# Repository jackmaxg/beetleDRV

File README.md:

# beetleDRV
Tiny brushed motor controller for 3lbs beetle weight combat robots

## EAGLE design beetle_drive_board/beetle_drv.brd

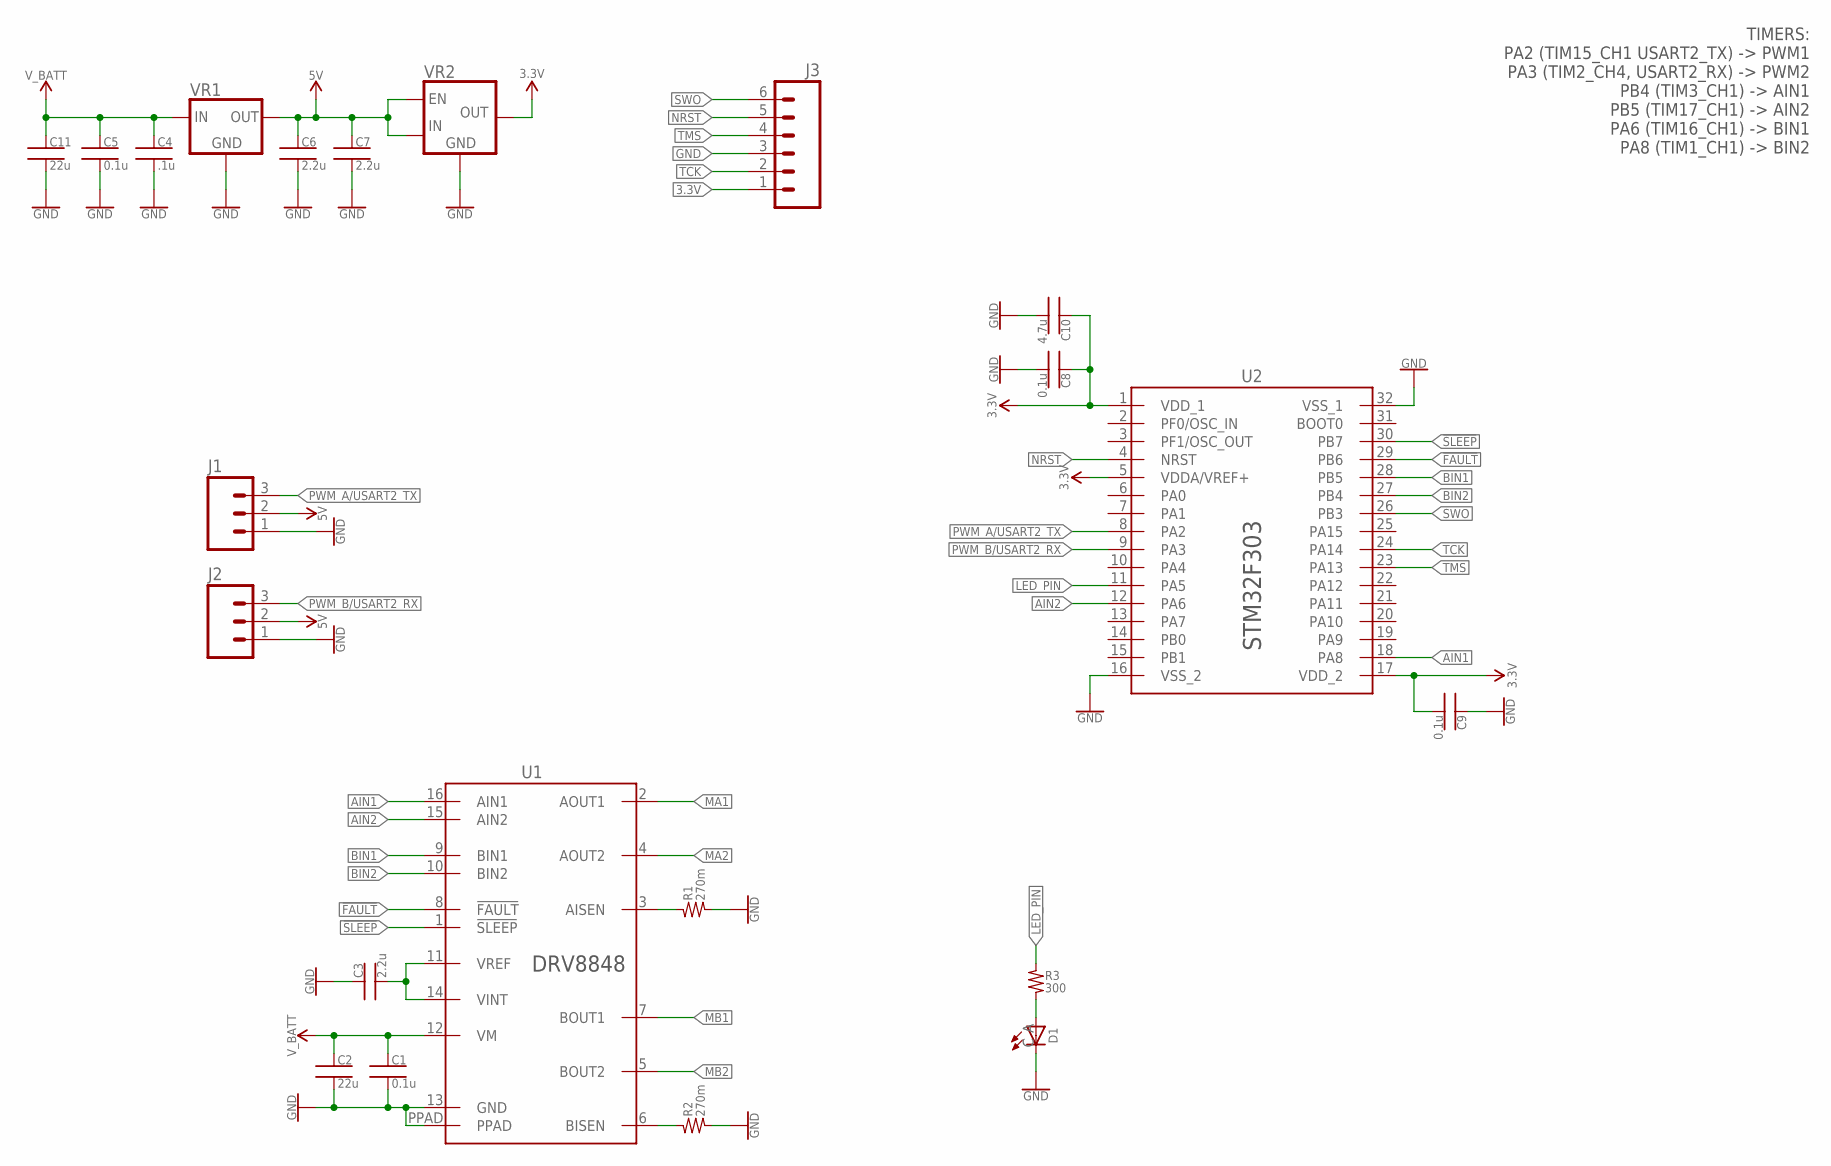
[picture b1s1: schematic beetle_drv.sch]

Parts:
C1, C5, C8, C9: 0.1u; 0603
C2, C11: 22u; 1210
C3, C6, C7: 2.2u; 0603
C4: .1u; 0603
C10: 4.7u; 0603
D1: LED1206; LED-1206
J1, J2: M03; 1X03
J3: SM06B-SRSS-TB
R1, R2: 270m; 1210
R3: 300; 0603
U1: DRV8848; PWP0016C
U2: STM32F303_LQFP32; LQFP32
VR1: 78XX_VREG_SOT223; SOT223-4
VR2: TLV733P_SOT23; SOT23-5

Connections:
3.3V: C8.1, C9.2, C10.1, J3.1, U2.1 (VDD_1), U2.5 (VDDA/VREF+), U2.17 (VDD_2), VR2.5 (OUT)
5V: C6.1, C7.1, J1.2, J2.2, VR1.3 (OUT), VR2.1 (IN), VR2.3 (EN)
!FAULT: U1.8 (!FAULT), U2.29 (PB6)
!SLEEP: U1.1 (!SLEEP), U2.30 (PB7)
AIN1: U1.16 (AIN1), U2.18 (PA8)
AIN2: U1.15 (AIN2), U2.12 (PA6)
AI_SEN: R1.1, U1.3 (AISEN)
BIN1: U1.9 (BIN1), U2.28 (PB5)
BIN2: U1.10 (BIN2), U2.27 (PB4)
BISEN: R2.1, U1.6 (BISEN)
GND: C1.2, C2.2, C3.1, C4.2, C5.2, C6.2, C7.2, C8.2, C9.1, C10.2, C11.2, D1.C, J1.1, J2.1, J3.3, R1.2, R2.2, U1.13 (GND), U1.PPAD, U2.16 (VSS_2), U2.32 (VSS_1), VR1.2 (GND), VR1.4 (GND), VR2.2 (GND), VR2.4 (GND)
LED_PIN: R3.1, U2.11 (PA5)
MA1: U1.2 (AOUT1)
MA2: U1.4 (AOUT2)
MB1: U1.7 (BOUT1)
MB2: U1.5 (BOUT2)
unnamed: D1.A, R3.2
NRST: J3.5, U2.4 (NRST)
PWM_A/USART2_TX: J1.3, U2.8 (PA2)
PWM_B/USART2_RX: J2.3, U2.9 (PA3)
SWO: J3.6, U2.26 (PB3)
TCK: J3.2, U2.24 (PA14)
TMS: J3.4, U2.23 (PA13)
VINT: C3.2, U1.11 (VREF), U1.14 (VINT)
V_BATT: C1.1, C2.1, C4.1, C5.1, C11.1, U1.12 (VM), VR1.1 (IN)

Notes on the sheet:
TIMERS: PA2 (TIM15_CH1 USART2_TX) -> PWM1 PA3 (TIM2_CH4, USART2_RX) -> PWM2 PB4 (TIM3_CH1) -> AIN1 PB5 (TIM17_CH1) -> AIN2 PA6 (TIM16_CH1) -> BIN1 PA8 (TIM1_CH1) -> BIN2

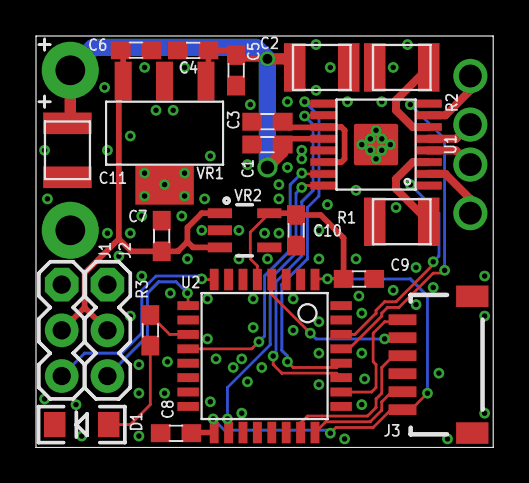
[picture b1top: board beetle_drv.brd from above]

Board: 2 copper layers, 25.4 x 22.9 mm, 22 parts (0 on the bottom side), 21 nets.

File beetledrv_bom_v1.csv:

Description,Part/parts,Mfr Part #,Digikey Part #,Qty/Board,Buy,Link
Motor Drive IC,U1,DRV8848,296-38514-5-ND,1,10,https://www.digikey.com/product-detail/en/DRV8848PWP/296-385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
.27 ohm current shunt,"R1, R2",ERJ-14BQFR27U,P17276CT-ND,2,20,https://www.digikey.com/product-detail/en/panasonic-electron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
0.3 ohm current shunt,"R1, R2",RCWE1210R300FKEA,RCWE.3FCT-ND,0,6,https://www.digikey.com/product-detail/en/vishay-dale/RCWE12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
0.5 ohm current shunt,"R1, R2",RCWE2512R500FKEA,541-4403-1-ND,0,6,https://www.digikey.com/product-detail/en/vishay-dale/RCWE25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
0.1uf 50v 0603 cap,"C1, C4, C5, C8, C9",CL10B104KB8NNNC,1276-1000-1-ND,6,100,https://www.digikey.com/product-detail/en/samsung-electro-me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
22uf 25v 1210 cap,"C2, C11",CL32B226KAJNFNE,1276-3391-1-ND,2,25,https://www.digikey.com/product-detail/en/samsung-electro-me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
2.2uF 16v 0603 cap,"C3, C6, C7",EMK107BB7225MA-T,587-4864-1-ND,3,40,https://www.digikey.com/product-detail/en/taiyo-yuden/EMK107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
5v linear reg,VR1,UA78M05CDCYR,296-12290-1-ND,1,10,https://www.digikey.com/product-detail/en/texas-instruments/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
5vTo3.3v reg,VR2,TLV73333PDBVR,296-40673-1-ND,1,10,https://www.digikey.com/product-detail/en/texas-instruments/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
4.7u 6.3v 0603 cap,C10,CL10A475KQ8NNNC,CL10A475KQ8NNNC,1,100,https://www.digikey.com/product-detail/en/samsung-electro-me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
Microcontroller,U2,STM32F303K8T6,497-15828-ND,1,10,https://www.digikey.com/products/en/integrated-circuits-ics/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
led 1206 2.1v green,D1,CMD15-21VGD/TR8,L62305CT-ND,1,15,https://www.digikey.com/product-detail/en/visual-communicati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
300 ohm 0603 res,R3,ERJ-3EKF3000V,P300HCT-ND,1,15,https://www.digikey.com/product-detail/en/panasonic-electron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
Prog Header RA 6pos,J3,SM06B-SRSS-TB(LF)(SN),455-1806-1-ND,1,12,https://www.digikey.com/product-detail/en/jst-sales-america-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
6pin jst cable assembly,,A06SR06SR30K152B,455-3015-ND,0,4,https://www.digikey.com/product-detail/en/jst-sales-america-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
3pin jst cable assembly,,A03SR03SR30K305B,455-3706-ND,0,1,https://www.digikey.com/product-detail/en/jst-sales-america-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

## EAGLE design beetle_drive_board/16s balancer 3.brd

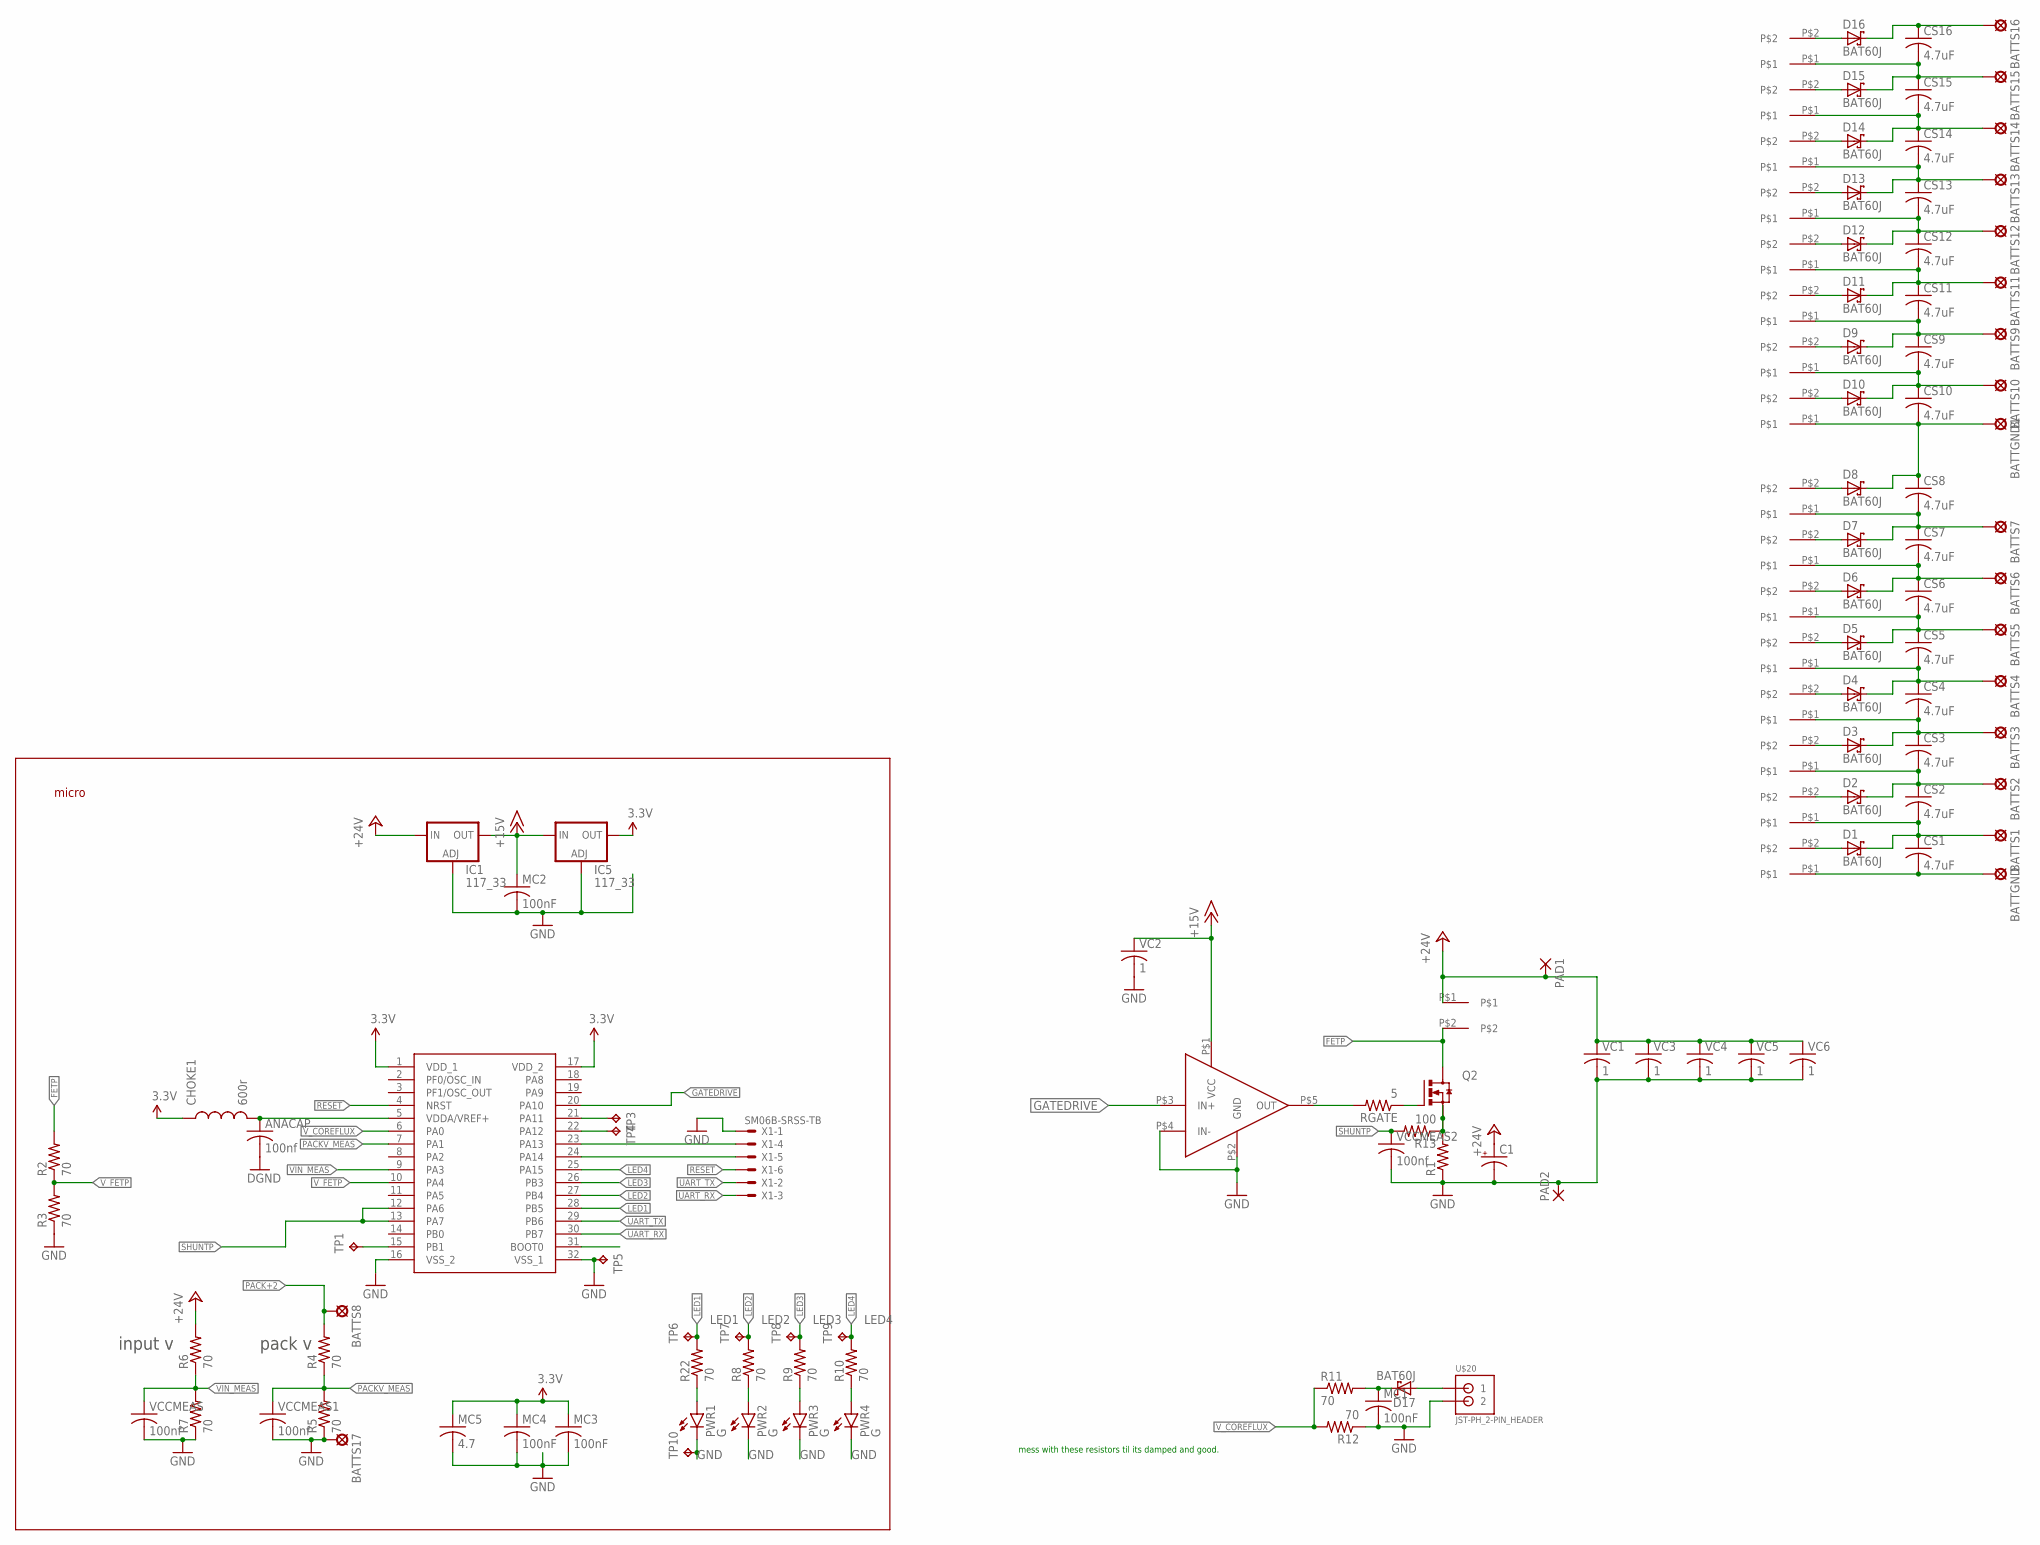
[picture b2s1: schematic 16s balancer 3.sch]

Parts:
ANACAP: 100nf; C0603
BATTGND, BATTGND1: LSP10
BATTS1, BATTS2, BATTS3, BATTS4, BATTS5, BATTS6, BATTS7, BATTS8, BATTS9, BATTS10, BATTS11, BATTS12, BATTS13, BATTS14, BATTS15, BATTS16, BATTS17: LSP10
C1: CPOL-USE2.5-7; E2,5-7
CHOKE1: 600r; 0603
CS1, CS2, CS3, CS4, CS5, CS6, CS7, CS8, CS9, CS10, CS11, CS12, CS13, CS14, CS15, CS16: 4.7uF; C1206
D1, D2, D3, D4, D5, D6, D7, D8, D9, D10, D11, D12, D13, D14, D15, D16, D17: BAT60J; SOD323_ST
IC1, IC5: 117_33; SOT223
MC1, MC2, MC3, MC4: 100nF; C0603
MC5: 4.7; C0603
PAD1, PAD2: 3,81/1,4
PWR1, PWR2, PWR3, PWR4: G; LED-0603
Q2: PH7030L; SOT669
R1: R-US_R0805; R0805
R2, R3, R4, R5, R6, R7, R8, R9, R10, R11, R12, R22: 70; R0603
R13: 100; R0603
RGATE: 5; R0603
TP1, TP3, TP4, TP5: TPTP10R; TP10R
TP6, TP7, TP8, TP9, TP10: TPTP14SQ; TP14SQ
U$1: STM32F303K8; LQFP32-7X7
U$2: UCC27517; SOT-23-5
U$3, U$4, U$5, U$6, U$7, U$8, U$9, U$10, U$11, U$12, U$13, U$14, U$15, U$16, U$17, U$18, U$19: LONG_PADS; LONG_PADS2
U$20: JST-PH_2-PIN_HEADER; JST_B2B-PH_HEADER
VC1, VC3, VC4, VC5, VC6: 1; C1206
VC2: 1; C0603
VCCMEAS, VCCMEAS1, VCCMEAS2: 100nf; C0603
X1: SM06B-SRSS-TB

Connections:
3.3V: CHOKE1.1, IC5.4 (OUT), MC3.1, MC4.1, MC5.1, U$1.1 (VDD_1), U$1.17 (VDD_2)
+15V: IC1.4 (OUT), IC5.3 (IN), MC2.1, U$2.P$1 (VCC), VC2.1
+24V: C1.+, IC1.3 (IN), PAD1.1, R6.2, U$3.P$1, VC1.1, VC3.1, VC4.1, VC5.1, VC6.1
CELL1: BATTS1.MP, CS1.1, CS2.2, D1.C, U$5.P$1
CELL2: BATTS2.MP, CS2.1, CS3.2, D2.C, U$6.P$1
CELL3: BATTS3.MP, CS3.1, CS4.2, D3.C, U$7.P$1
CELL4: BATTS4.MP, CS4.1, CS5.2, D4.C, U$8.P$1
CELL5: BATTS5.MP, CS5.1, CS6.2, D5.C, U$9.P$1
CELL6: BATTS6.MP, CS6.1, CS7.2, D6.C, U$10.P$1
CELL7: BATTS7.MP, CS7.1, CS8.2, D7.C, U$11.P$1
CELL8: BATTGND1.MP, CS8.1, CS10.2, D8.C, U$13.P$1
CELL9: BATTS10.MP, CS9.2, CS10.1, D10.C, U$12.P$1
CELL10: BATTS11.MP, CS11.1, CS12.2, D11.C, U$15.P$1
CELL11: BATTS9.MP, CS9.1, CS11.2, D9.C, U$14.P$1
CELL12: BATTS12.MP, CS12.1, CS13.2, D12.C, U$16.P$1
CELL13: BATTS14.MP, CS14.1, CS15.2, D14.C, U$18.P$1
CELL14: BATTS13.MP, CS13.1, CS14.2, D13.C, U$17.P$1
CELL16: BATTS15.MP, CS15.1, CS16.2, D15.C, U$19.P$1
FETP: Q2.MB (D), R2.2, U$3.P$2
GATEDRIVE: U$1.20 (PA10), U$2.P$3 (IN+)
GND: ANACAP.2, BATTS17.MP, C1.-, IC1.1 (ADJ), IC5.1 (ADJ), MC1.2, MC2.2, MC3.2, MC4.2, MC5.2, PAD2.1, PWR1.C, PWR2.C, PWR3.C, PWR4.C, R1.1, R3.1, R5.1, R7.1, R12.1, TP5.TP, TP10.TP, U$1.16 (VSS_2), U$1.32 (VSS_1), U$2.P$2 (GND), U$2.P$4 (IN-), U$20.P2 (2), VC1.2, VC2.2, VC3.2, VC4.2, VC5.2, VC6.2, VCCMEAS.2, VCCMEAS1.2, VCCMEAS2.2, X1.1
LED1: R22.2, TP6.TP, U$1.28 (PB5)
LED2: R8.2, TP7.TP, U$1.27 (PB4)
LED3: R9.2, TP8.TP, U$1.26 (PB3)
LED4: R10.2, TP9.TP, U$1.25 (PA15)
unnamed: D17.A, U$20.P1 (1)
unnamed: TP1.TP, U$1.15 (PB1)
unnamed: D9.A, U$12.P$2
unnamed: D4.A, U$7.P$2
unnamed: D2.A, U$5.P$2
unnamed: D10.A, U$13.P$2
unnamed: D11.A, U$14.P$2
unnamed: D1.A, U$4.P$2
unnamed: D3.A, U$6.P$2
unnamed: D12.A, U$15.P$2
unnamed: D13.A, U$16.P$2
unnamed: D14.A, U$17.P$2
unnamed: D5.A, U$8.P$2
unnamed: D15.A, U$18.P$2
unnamed: D6.A, U$9.P$2
unnamed: D16.A, U$19.P$2
unnamed: D7.A, U$10.P$2
unnamed: D8.A, U$11.P$2
unnamed: PWR2.A, R8.1
unnamed: Q2.4 (G), RGATE.1
unnamed: RGATE.2, U$2.P$5 (OUT)
unnamed: PWR3.A, R9.1
unnamed: PWR4.A, R10.1
unnamed: BATTGND.MP, CS1.2, U$4.P$1
unnamed: D17.C, MC1.1, R11.2
unnamed: PWR1.A, R22.1
PACK+: BATTS16.MP, CS16.1, D16.C
PACK+2: BATTS8.MP, R4.2
PACKV_MEAS: R4.1, R5.2, U$1.7 (PA1), VCCMEAS1.1
PROG1: U$1.23 (PA13), X1.4
PROG2: U$1.24 (PA14), X1.5
PWM1_N: TP3.TP, U$1.21 (PA11)
PWM2_N: TP4.TP, U$1.22 (PA12)
RESET: U$1.4 (NRST), X1.6
SHUNTP: R13.2, U$1.12 (PA6), U$1.13 (PA7), VCCMEAS2.1
SHUNTP-NF: Q2.1 (S), Q2.2 (S), Q2.3 (S), R1.2, R13.1
UART_RX: U$1.30 (PB7), X1.3
UART_TX: U$1.29 (PB6), X1.2
VDDA: ANACAP.1, CHOKE1.2, U$1.5 (VDDA/VREF+)
VIN_MEAS: R6.1, R7.2, U$1.9 (PA3), VCCMEAS.1
V_COREFLUX: R11.1, R12.2, U$1.6 (PA0)
V_FETP: R2.1, R3.2, U$1.10 (PA4)

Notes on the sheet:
micro
mess with these resistors til its damped and good.
input v
pack v

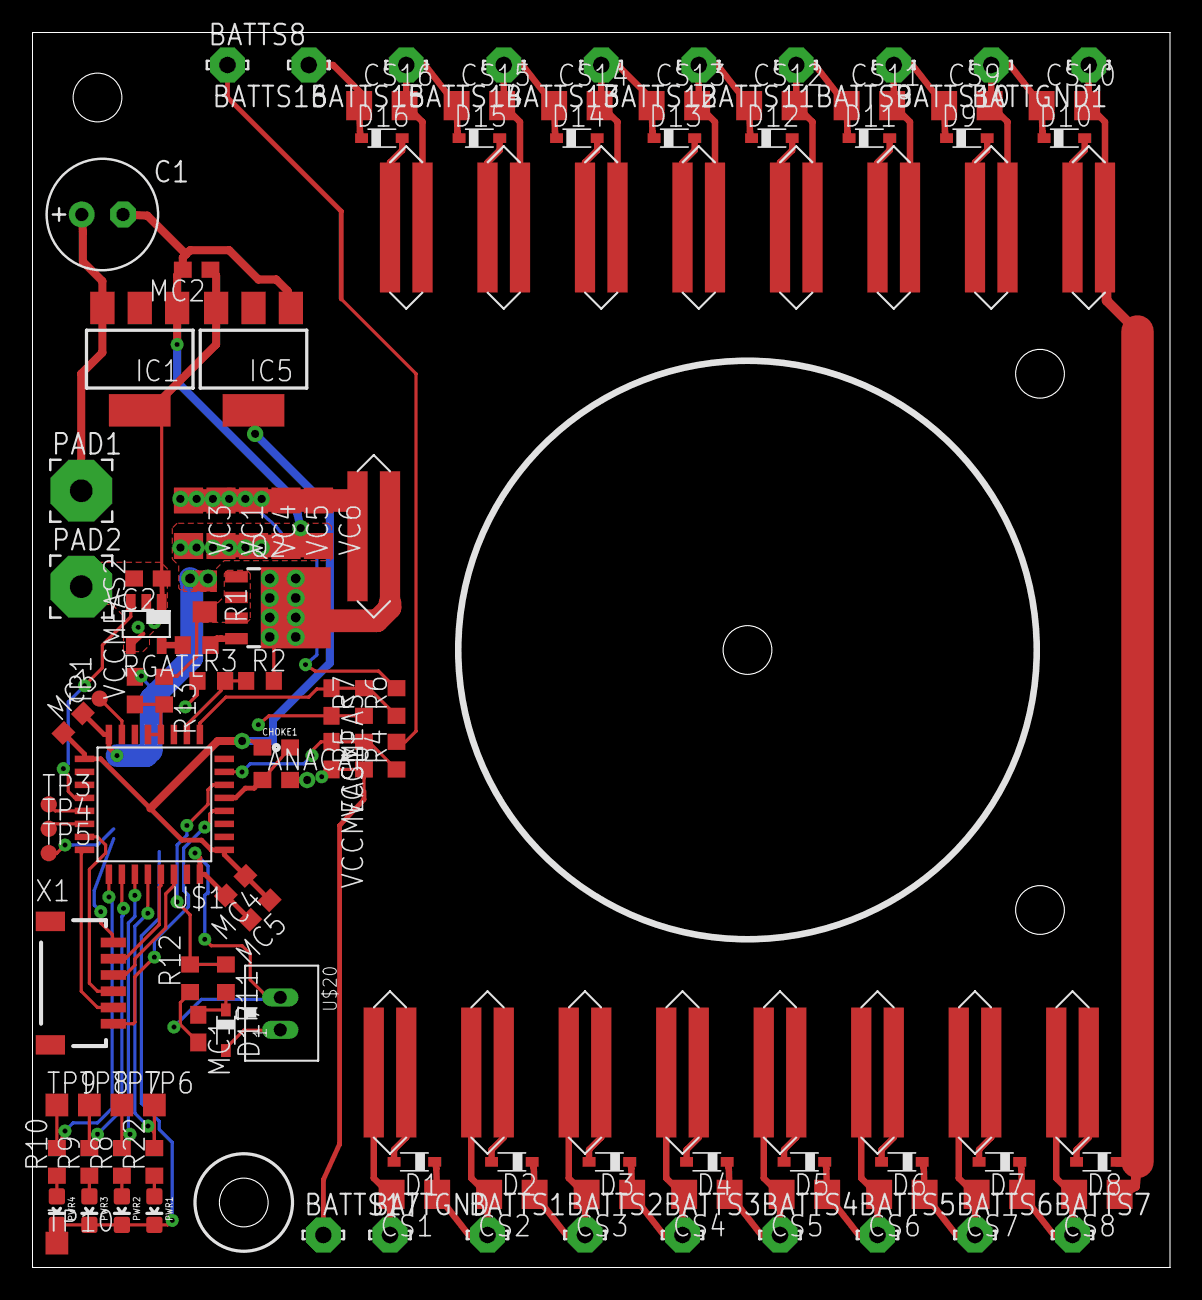
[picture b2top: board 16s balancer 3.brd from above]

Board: 2 copper layers, 70.0 x 76.0 mm, 123 parts (0 on the bottom side), 67 nets.

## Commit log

2020-01-09 inital commit with v1 of the board finished, finally got around to making a repo for this project

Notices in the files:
parts and their libraries:
SparkFun-Passives: Licensing: Creative Commons ShareAlike 4.0 International - https://creativecommons.org/licenses/by-sa/4.0
